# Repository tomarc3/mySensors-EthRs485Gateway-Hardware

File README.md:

# mySensors-EthRs485Gateway-Hardware

The mySensors-EthRs485Gateway-Hardware is a mySensors compatible Ethernet / RS485 gateway that is designed to fit in a DIN rail enclosure.

The PCB dimensions are designed to fit in a [CAMDENBOSS CNMB/2/KIT DIN](http://camdenboss.com/enclosures/din-rail-enclosures/cnmb-solid-top-kit) rail enclosure - with a litte mod... ;) 

The firmware that works with this gateway can be found at https://github.com/tomarc3/mySensors-EthRs485Gateway

The front panel:

## Refereneces
* https://github.com/tomarc3/mySensors-EthRs485Gateway - the firmware built to run on this hardware
* https://www.mysensors.org - mySensors home page
* https://www.mysensors.org/build/rs485 - the example sketch that served as reference for this project 
* http://camdenboss.com/enclosures/din-rail-enclosures/cnmb-solid-top-kit - CAMDENBOSS CNMB/2/KIT DIN rail enclosure

## Change Log
* v1.0 ()
   Initial version.

## License
Copyright 2018 by Tom Kocher.

This documentation describes Open Hardware and is licensed under the CERN OHL v.1.2.

You may redistribute and modify this documentation under the terms of the CERN OHL v.1.2. (http://ohwr.org/cernohl). This documentation is distributed WITHOUT ANY EXPRESS OR IMPLIED WARRANTY, INCLUDING OF MERCHANTABILITY, SATISFACTORY QUALITY AND FITNESS FOR A PARTICULAR PURPOSE. Please see the CERN OHL v.1.2 for applicable conditions

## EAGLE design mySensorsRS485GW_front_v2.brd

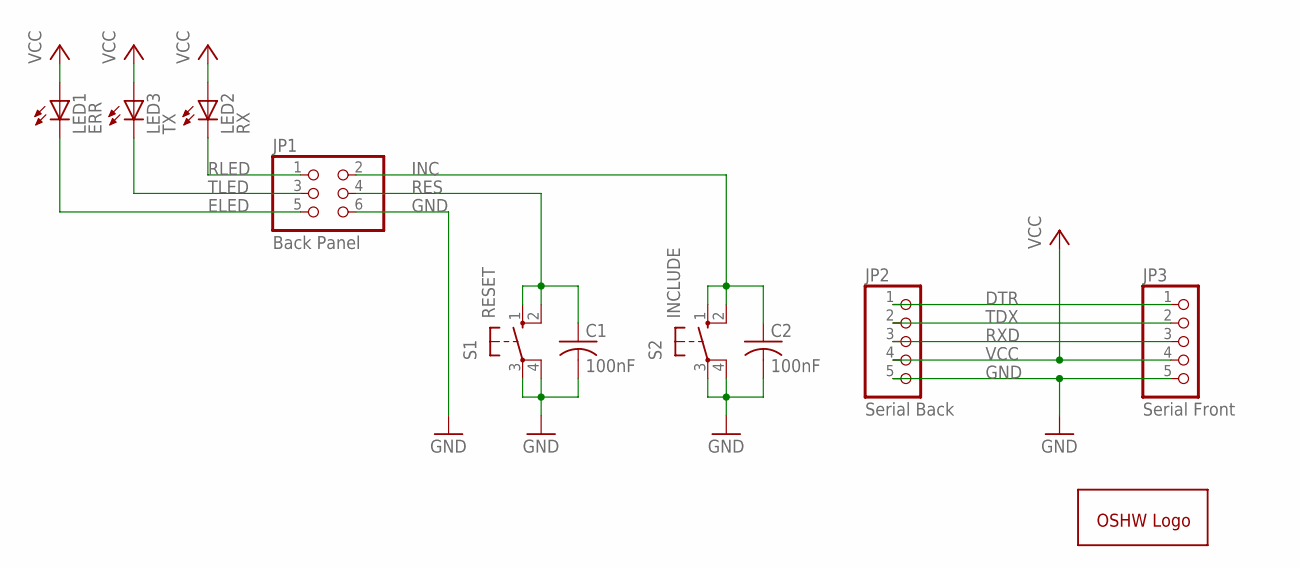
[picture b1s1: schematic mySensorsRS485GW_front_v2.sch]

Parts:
C1, C2: 100nF; C025-025X050
GOLD_ORB_SM1: OSHWLOGOLOGO5MM; OSHW_5MM
JP1: Back Panel; 2X03
JP2: Serial Back; 1X05
JP3: Serial Front; 1X05
LED1: ERR; LED3MM
LED2: RX; LED3MM
LED3: TX; LED3MM
S1: RESET; B3F-10XX
S2: INCLUDE; B3F-10XX

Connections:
DTR: JP2.1, JP3.1
ELED: JP1.5, LED1.K (C)
GND: C1.2, C2.2, JP1.6, JP2.5, JP3.5, S1.3, S1.4 (P1), S2.3, S2.4 (P1)
INC: C2.1, JP1.2, S2.1 (S), S2.2 (S1)
RES: C1.1, JP1.4, S1.1 (S), S1.2 (S1)
RLED: JP1.1, LED2.K (C)
RXD: JP2.3, JP3.3
TDX: JP2.2, JP3.2
TLED: JP1.3, LED3.K (C)
VCC: JP2.4, JP3.4, LED1.A, LED2.A, LED3.A

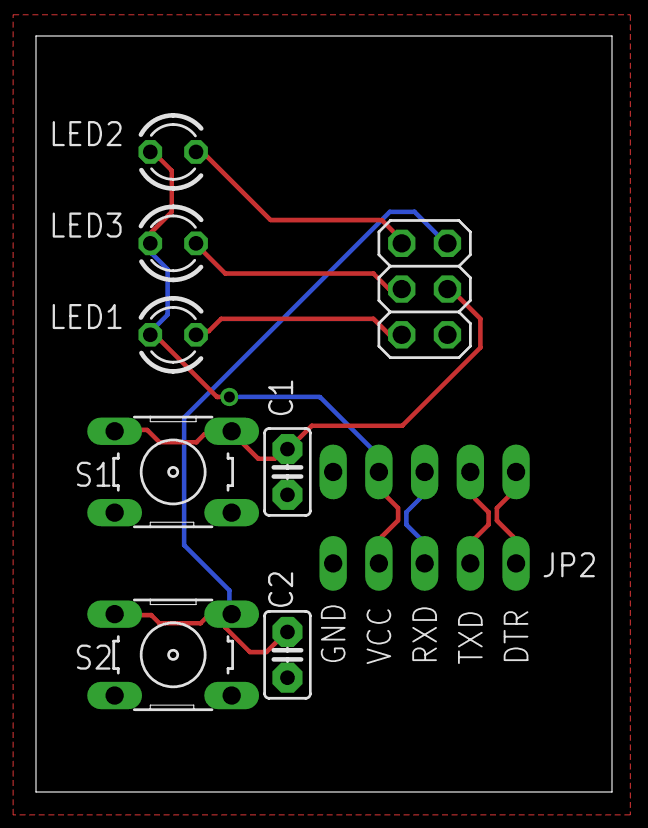
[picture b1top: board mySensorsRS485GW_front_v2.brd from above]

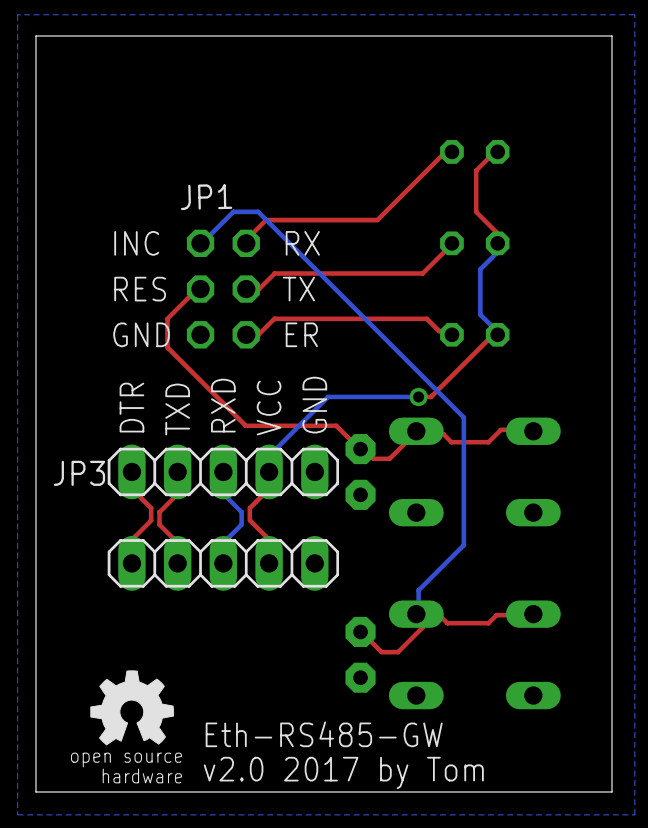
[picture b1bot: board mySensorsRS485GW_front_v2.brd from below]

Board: 2 copper layers, 32.0 x 42.0 mm, 11 parts (3 on the bottom side), 10 nets.

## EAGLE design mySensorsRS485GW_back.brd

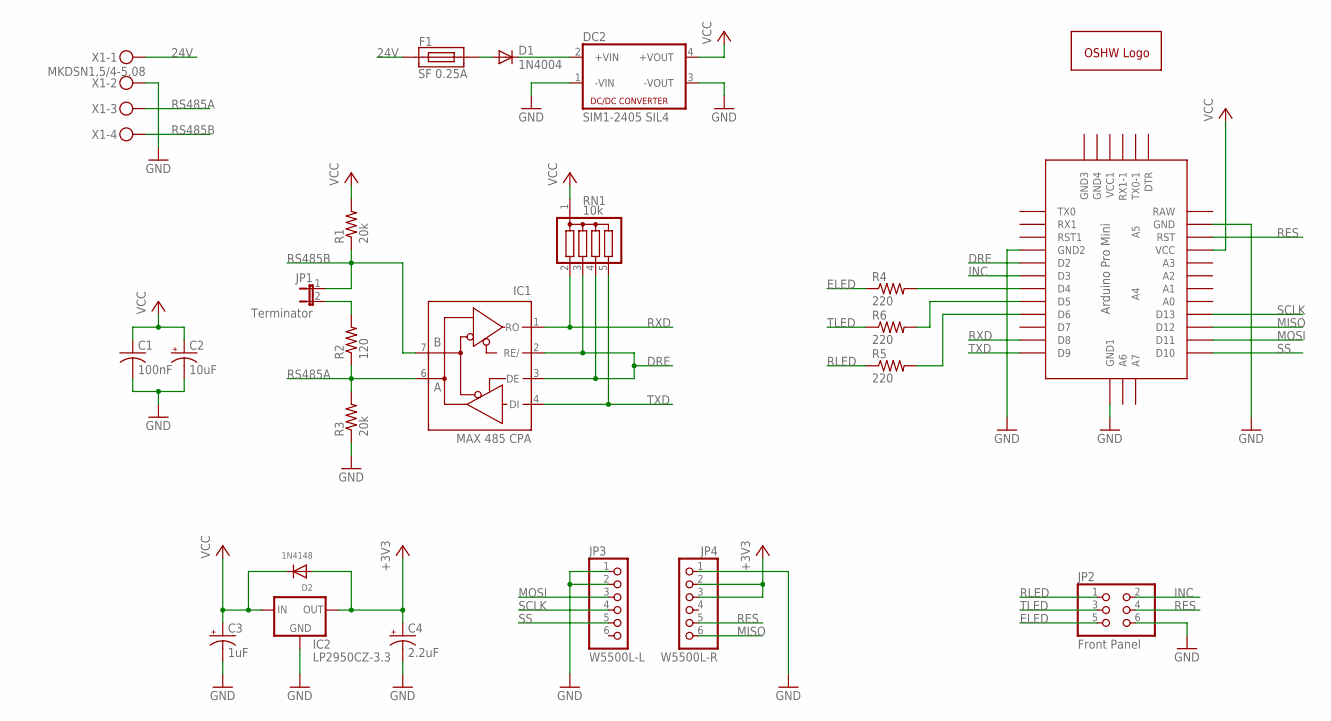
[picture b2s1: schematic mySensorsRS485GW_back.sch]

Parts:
C1: 100nF; C025-025X050
C2: 10uF; TT2D5
C3: 1uF; TT2D5
C4: 2.2uF; TT2D5
D1: 1N4004; DO41-10
D2: 1N4148; DO-1N4148
DC2: SIM1-2405 SIL4; NME
F1: SF 0.25A; NANO2_SMF_FUSEBLOCK
GOLD_ORB_SM1: OSHWLOGOLOGO5MM; OSHW_5MM
IC1: MAX 485 CPA; DIL08
IC2: LP2950CZ-3.3; TO92
JP1: Terminator; JP1
JP2: Front Panel; 2X03
JP3: W5500L-L; 1X06
JP4: W5500L-R; 1X06
R1, R3: 20k; 0207/2V
R2: 120; 0207/2V
R4, R5, R6: 220; 0207/7
RN1: 10k; SIL5
U$1: ABK-PRO-MINI
X1: MKDSN1,5/4-5,08

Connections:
24V: F1.1, X1.1
+3V3: C4.+, D2.A, IC2.1 (OUT), JP4.2, JP4.3
DRE: IC1.2 (RE/), IC1.3 (DE), RN1.3, RN1.4, U$1.D2
ELED: JP2.5, R4.1
GND: C1.2, C2.-, C3.-, C4.-, DC2.1 (-VIN), DC2.3 (-VOUT), IC1.5 (GND), IC2.2 (GND), JP2.6, JP3.1, JP3.2, JP4.1, R3.1, U$1.GND, U$1.GND1 (GND2), U$1.GND4 (GND1), X1.2
INC: JP2.2, U$1.D3
MISO: JP4.6, U$1.D12
MOSI: JP3.3, U$1.D11
unnamed: R4.2, U$1.D4
unnamed: D1.A, F1.2
unnamed: D1.C, DC2.2 (+VIN)
unnamed: R6.2, U$1.D5
unnamed: R5.2, U$1.D6
unnamed: JP1.2, R2.2
RES: JP2.4, JP4.5, U$1.RST
RLED: JP2.1, R5.1
RS485A: IC1.6 (A), R2.1, R3.2, X1.3
RS485B: IC1.7 (B), JP1.1, R1.1, X1.4
RXD: IC1.1 (RO), RN1.2, U$1.D8
SCLK: JP3.4, U$1.D13
SS: JP3.5, U$1.D10
TLED: JP2.3, R6.1
TXD: IC1.4 (DI), RN1.5, U$1.D9
VCC: C1.1, C2.+, C3.+, D2.C, DC2.4 (+VOUT), IC1.8 (VCC), IC2.3 (IN), R1.2, RN1.1, U$1.VCC

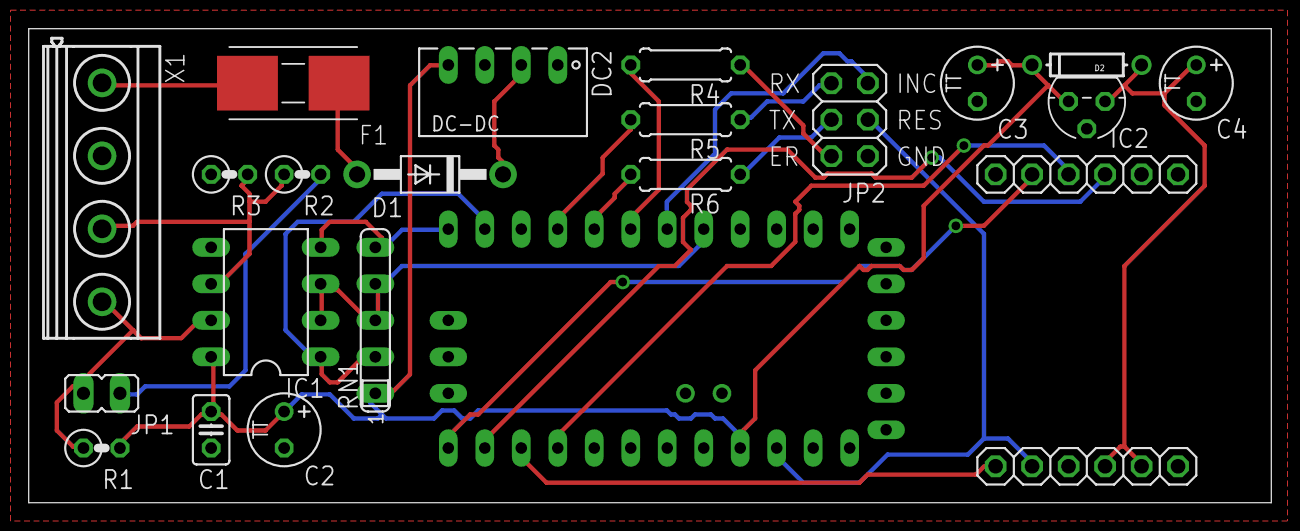
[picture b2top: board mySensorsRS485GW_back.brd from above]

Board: 2 copper layers, 86.5 x 33.0 mm, 24 parts (1 on the bottom side), 24 nets.

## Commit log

2018-03-27 Applied CERN OHL v1.2 License
